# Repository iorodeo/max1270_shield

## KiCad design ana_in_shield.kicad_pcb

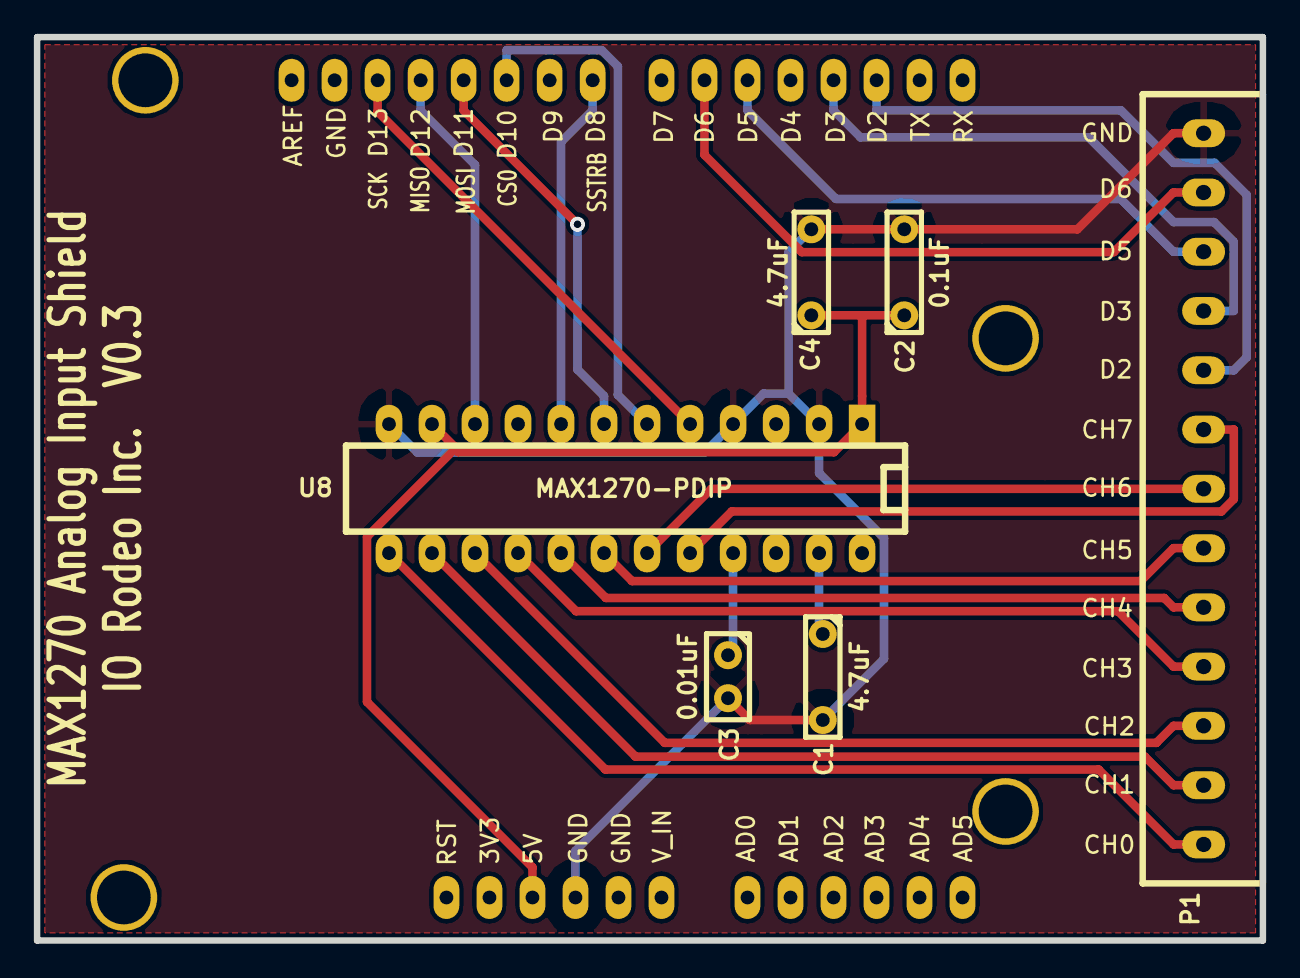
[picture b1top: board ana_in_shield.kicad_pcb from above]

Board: 2 copper layers, 72.4 x 53.4 mm, 7 parts (0 on the bottom side), 21 nets.

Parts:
C1, C4: 4.7uF; C2_Big_Pad
C2: 0.1uF; C2_Big_Pad
C3: 0.01uF; C1_Big_Pad
P1: CONN_13
SHIELD1: ARDUINO_SHIELD
U8: MAX1270-PDIP; DIP-24__300_ELL

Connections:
/5V: C2.1, C4.1, SHIELD1.5V, U8.1, U8.11
/CH0: P1.1, U8.13
/CH1: P1.2, U8.14
/CH2: P1.3, U8.15
/CH3: P1.4, U8.16
/CH4: P1.5, U8.17
/CH5: P1.6, U8.18
/CH6: P1.7, U8.19
/CH7: P1.8, U8.20
/CS0: SHIELD1.10, U8.6
/D2: P1.9, SHIELD1.2
/D3: P1.10, SHIELD1.3
/D5: P1.11, SHIELD1.5
/D6: P1.12, SHIELD1.6
/MISO: SHIELD1.12, U8.10
/MOSI: SHIELD1.11, U8.7
/SCK: SHIELD1.13, U8.5
/SSTRB: SHIELD1.8, U8.8
GND: C1.2, C2.2, C3.2, C4.2, P1.13, SHIELD1.GND1, U8.2, U8.4, U8.12
unnamed: C3.1, U8.21
unnamed: C1.1, U8.23

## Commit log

2012-09-15 Project creation.
2012-09-24 Fixed minor error in board due to mis-numbering of the pins of the 13 pin connector. Re-made gerber files.
2012-09-24 Fixed mislabeling of RX and TX on silkscreen.
2013-08-24 Fixed some issues - pads too small, mislabeled DIO.
2013-08-24 Fixed issues with references.
2013-08-24 Created v0.2 version of gerber files.
2017-11-10 Added pdf of schematic.
2017-12-21 Added version 0.3 of gerber files. Fixed spelling error in silk screen.
